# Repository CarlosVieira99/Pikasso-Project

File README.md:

# Pikasso-Project
Bachelor Project with a final classification of 19 (scale of 0 - 20). Drawing and writing machine, controlled via Wi-Fi, with a graphical interface on the computer. Developed with C and Python.

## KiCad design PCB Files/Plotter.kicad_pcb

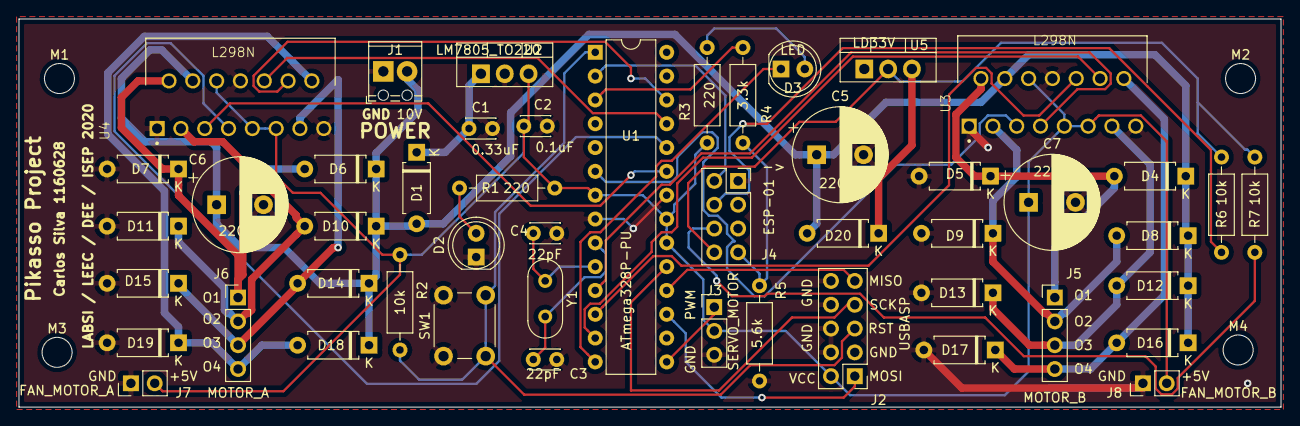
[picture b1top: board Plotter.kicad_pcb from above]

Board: 2 copper layers, 134.6 x 41.4 mm, 53 parts (0 on the bottom side), 37 nets.

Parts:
C1: 0.33uF; C_Disc_D3.0mm_W2.0mm_P2.50mm
C2: 0.1uF; C_Disc_D3.0mm_W2.0mm_P2.50mm
C3, C4: 22pF; C_Disc_D3.0mm_W2.0mm_P2.50mm
C5, C6, C7: 220uF; CP_Radial_D10.0mm_P5.00mm
D1, D4, D5, D6, D7, D8, D9, D10, D11, D12, D13, D14, D15, D16, D17, D18, D19, D20: D; D_A-405_P7.62mm_Horizontal
D2, D3: LED; LED_D5.0mm
J1: 10V; TerminalBlock_Phoenix_MPT-0,5-2-2.54_1x02_P2.54mm_Horizontal
J2: USBASP; PinHeader_2x05_P2.54mm_Vertical
J3: SERVO_MOTOR; PinHeader_1x03_P2.54mm_Vertical
J4: ESP-01; PinSocket_2x04_P2.54mm_Vertical
J5: MOTOR_B; PinHeader_1x04_P2.54mm_Vertical
J6: MOTOR_A; PinHeader_1x04_P2.54mm_Vertical
J7: FAN_MOTOR_A; PinHeader_1x02_P2.54mm_Vertical
J8: FAN_MOTOR_B; PinHeader_1x02_P2.54mm_Vertical
M1, M2, M3, M4: MountingHole_3.2mm_M3
R1, R3: 220; R_Axial_DIN0207_L6.3mm_D2.5mm_P10.16mm_Horizontal
R2, R6, R7: 10k; R_Axial_DIN0207_L6.3mm_D2.5mm_P10.16mm_Horizontal
R4: 3.3k; R_Axial_DIN0207_L6.3mm_D2.5mm_P10.16mm_Horizontal
R5: 5.6k; R_Axial_DIN0207_L6.3mm_D2.5mm_P10.16mm_Horizontal
SW1: SW_Push; SW_PUSH_6mm
U1: ATmega328P-PU; DIP-28_W7.62mm
U2: LM7805_TO220; TO-220-3_Vertical
U3, U4: L298N; TO127P2020X500X2100-15
U5: LD33V; TO-220-3_Vertical
Y1: Crystal; Crystal_HC52-6mm_Vertical

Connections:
+3V3: J4.8, R6.2, R7.2, U5.2
+5V: C2.1, C7.1, J2.2, J3.2, J7.2, J8.2, R1.1, R2.1, R3.1, U1.7, U1.20, U1.21, U2.3, U3.6, U3.9, U3.11, U4.6, U4.9, U4.11
+10V: C5.1, C6.1, D1.2, D4.1, D6.1, D8.1, D10.1, D12.1, D14.1, D16.1, D18.1, D20.2, J1.2, U3.4, U4.4
BLINK: D3.1, U1.14
GND: C1.2, C2.2, C3.2, C4.2, C5.2, C6.2, C7.2, D2.1, D5.2, D7.2, D9.2, D11.2, D13.2, D15.2, D17.2, D19.2, J1.1, J2.4, J2.6, J2.8, J2.10, J3.3, J4.1, J7.1, J8.1, R5.2, SW1.1, U1.8, U1.22, U2.2, U3.1, U3.8, U3.15, U4.1, U4.8, U4.15, U5.1
IN1A: U1.23, U4.5
IN1B: U1.6, U3.5
IN2A: U1.24, U4.7
IN2B: U1.11, U3.7
IN3A: U1.25, U4.10
IN3B: U1.12, U3.10
IN4A: U1.26, U4.12
IN4B: U1.13, U3.12
MISO: J2.9, U1.18
MOSI: J2.1, U1.17
unnamed: C1.1, D1.1, U2.1
unnamed: D2.2, R1.2
unnamed: D3.2, R3.2
unnamed: D4.2, D5.1, J5.1, U3.2
unnamed: D6.2, D7.1, J6.1, U4.2
unnamed: D8.2, D9.1, J5.2, U3.3
unnamed: D10.2, D11.1, J6.2, U4.3
unnamed: D12.2, D13.1, J5.3, U3.13
unnamed: D14.2, D15.1, J6.3, U4.13
unnamed: D16.2, D17.1, J5.4, U3.14
unnamed: D18.2, D19.1, J6.4, U4.14
unnamed: D20.1, U5.3
unnamed: J4.4, R6.1
unnamed: J4.6, R7.1
RESET: J2.5, R2.2, SW1.2, U1.1
RX_ATMEGA: J4.2, U1.2
RX_ESP: J4.7, R4.2, R5.1
SCK: J2.7, U1.19
SERVO: J3.1, U1.15
TX_ATMEGA: R4.1, U1.3
XTAL1: C3.1, U1.9, Y1.2
XTAL2: C4.1, U1.10, Y1.1
